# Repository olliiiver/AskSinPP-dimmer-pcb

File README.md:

# Homematic 5-channel LED dimmer PCB for Arduino using CC1101 (KiCad)

Arduino sketch can be found here:

https://github.com/olliiiver/AskSinPP-rgbwwcw-dimmer

## Features

- 12-24 volt
- 256-step 97 kHz PWM
- TTH or SMD for filter capacitors 

## BOM

- PCA9634PW
- Arduino Pro Mini https://store.arduino.cc/arduino-pro-mini
- CC1101 board (from eBay)
- N-Channel MOSFET (IRL540N 30A 100V)
- Recom R-78E5.0-0.5
- AMS1117-3.3
- 10K resistors
- 100 nF / 10 uF capacitors

## TODO

- Add ground pad

## Images

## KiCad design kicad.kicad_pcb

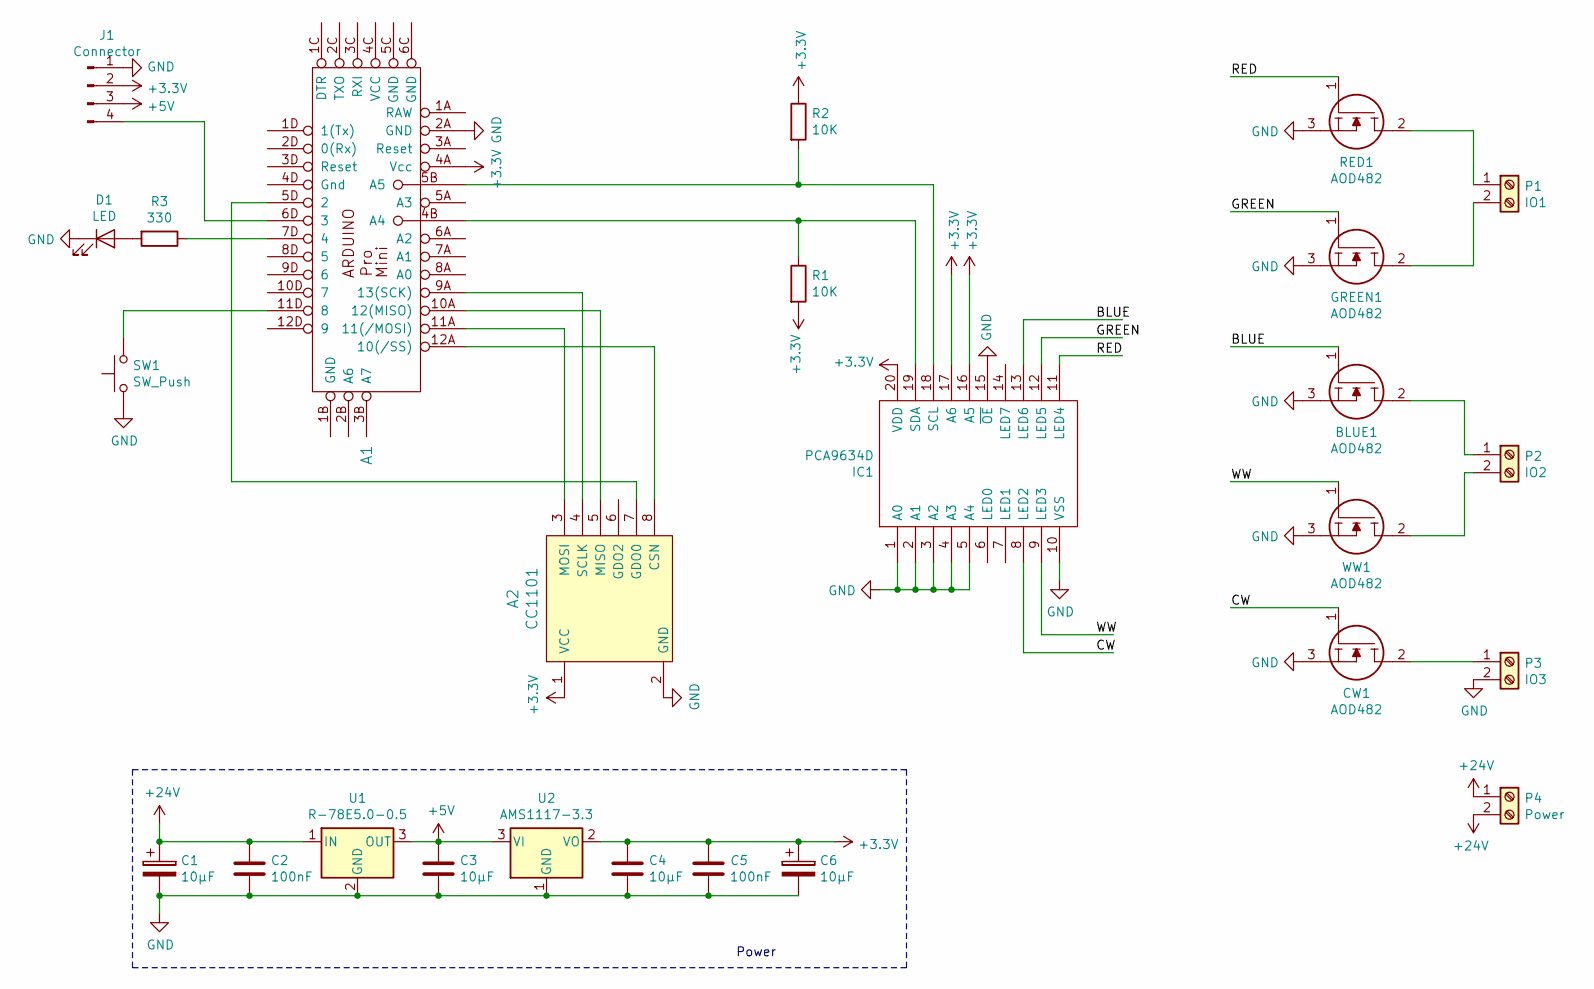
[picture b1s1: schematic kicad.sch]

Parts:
A1: Arduino_Pro_Mini
A2: CC1101; cc1101
BLUE1: AOD482; TO-252-2; Manufacturer_Part_Number IRL540NPBF; Mouser Part Number 942-IRL540NPBF
C1, C6: 10µF; CP_Radial_D5.0mm_P2.00mm
C2, C5: 100nF; C_Disc_D3.0mm_W2.0mm_P2.50mm
C3, C4: 10µF; C_0805_2012Metric_Pad1.15x1.40mm_HandSolder
CW1: AOD482; TO-252-2; Manufacturer_Part_Number IRL540NPBF; Mouser Part Number 942-IRL540NPBF
D1: LED; LED_D3.0mm
GREEN1: AOD482; TO-252-2; Manufacturer_Part_Number IRL540NPBF; Mouser Part Number 942-IRL540NPBF
IC1: PCA9634D; Manufacturer_Part_Number PCA9634D; Mouser Part Number 771-PCA9634D
J1: Connector; PinHeader_1x04_P2.54mm_Vertical
P1: IO1; TerminalBlock_bornier-2_P5.08mm
P2: IO2; TerminalBlock_bornier-2_P5.08mm
P3: IO3; TerminalBlock_bornier-2_P5.08mm
P4: Power; TerminalBlock_bornier-2_P5.08mm
R1, R2: 10K; R_0805_2012Metric_Pad1.15x1.40mm_HandSolder
R3: 330; R_0805_2012Metric_Pad1.15x1.40mm_HandSolder
RED1: AOD482; TO-252-2; Manufacturer_Part_Number IRL540NPBF; Mouser Part Number 942-IRL540NPBF
SW1: SW_Push; SW_PUSH_6mm
U1: R-78E5.0-0.5; Converter_DCDC_RECOM_R-78E-0.5_THT
U2: AMS1117-3.3; SOT-223-3_TabPin2
WW1: AOD482; TO-252-2; Manufacturer_Part_Number IRL540NPBF; Mouser Part Number 942-IRL540NPBF

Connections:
+3V3: A1.4A (Vcc), A2.1 (VCC), C4.1, C5.1, C6.1, IC1.16 (A5), IC1.17 (A6), IC1.20 (VDD), J1.2, R1.2, R2.1, U2.2 (VO)
+5V: C3.1, J1.3, U1.3 (OUT), U2.3 (VI)
+24V: C1.1, C2.1, P4.1, P4.2, U1.1 (IN)
/BLUE: BLUE1.1, IC1.13 (LED6)
/CW: CW1.1, IC1.8 (LED2)
/GREEN: GREEN1.1, IC1.12 (LED5)
/RED: IC1.11 (LED4), RED1.1
/WW: IC1.9 (LED3), WW1.1
GND: A1.2A (GND), A2.2 (GND), BLUE1.3, C1.2, C2.2, C3.2, C4.2, C5.2, C6.2, CW1.3, D1.1 (K), GREEN1.3, IC1.1 (A0), IC1.2 (A1), IC1.3 (A2), IC1.4 (A3), IC1.5 (A4), IC1.10 (VSS), IC1.15 (~OE), J1.1, P3.2, RED1.3, SW1.1, U1.2 (GND), U2.1 (GND), WW1.3
unnamed: A1.4B (A4), IC1.19 (SDA), R1.1
unnamed: A1.5B (A5), IC1.18 (SCL), R2.2
unnamed: A1.5D (2), A2.7 (GDO0)
unnamed: A1.6D (3), J1.4
unnamed: A1.7D (4), R3.1
unnamed: A1.9A (13(SCK)), A2.4 (SCLK)
unnamed: A1.10A (12(MISO)), A2.5 (MISO)
unnamed: A1.11A (11(/MOSI)), A2.3 (MOSI)
unnamed: A1.11D (8), SW1.2
unnamed: A1.12A (10(/SS)), A2.8 (CSN)
unnamed: BLUE1.2, P2.1
unnamed: CW1.2, P3.1
unnamed: D1.2 (A), R3.2
unnamed: GREEN1.2, P1.2
unnamed: P1.1, RED1.2
unnamed: P2.2, WW1.2

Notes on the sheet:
Power

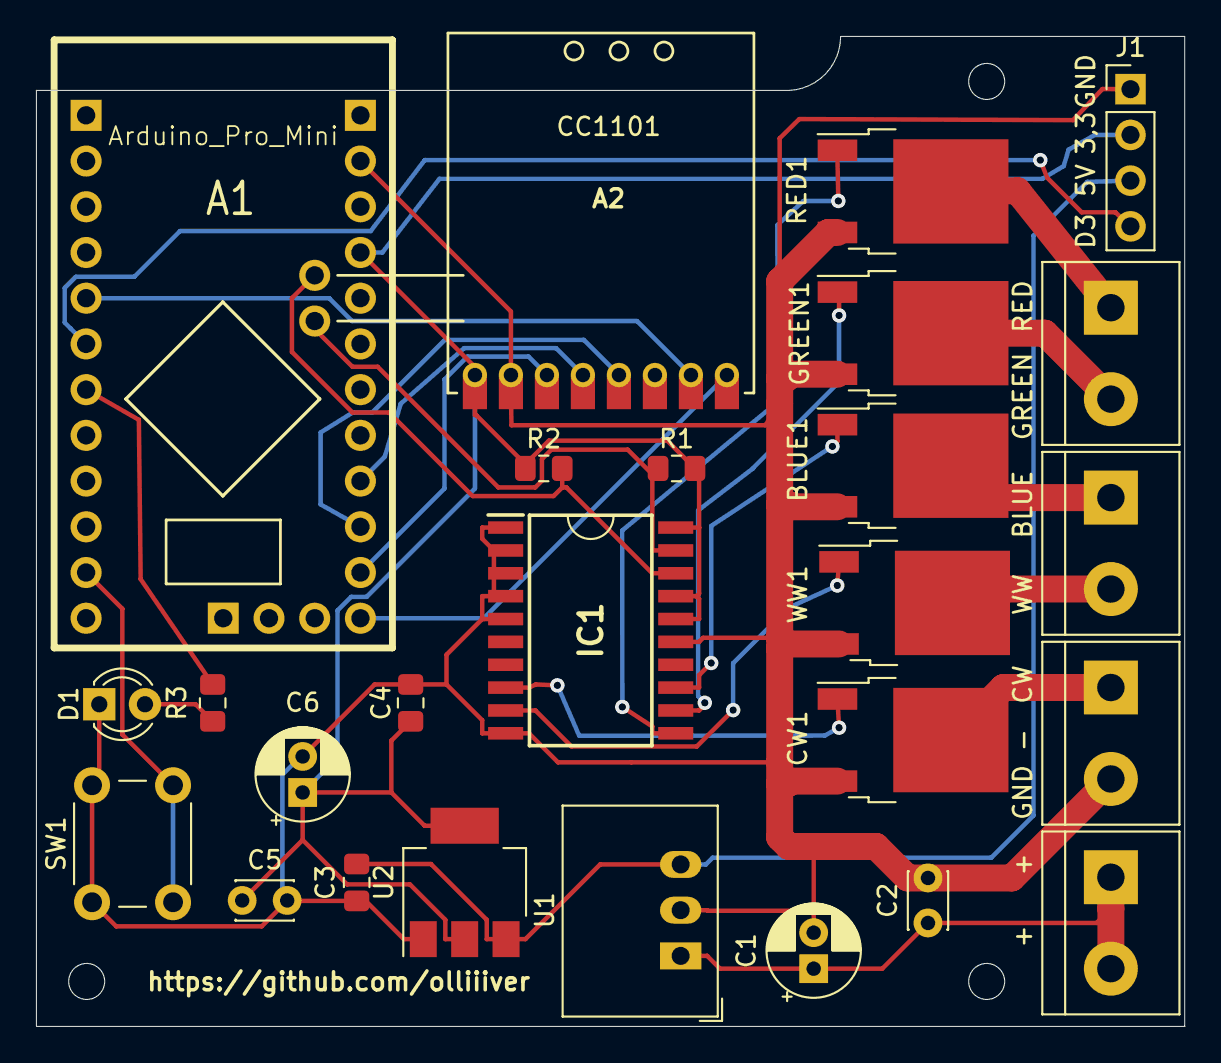
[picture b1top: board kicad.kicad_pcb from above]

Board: 2 copper layers, 63.8 x 55.0 mm, 29 parts (0 on the bottom side), 25 nets.

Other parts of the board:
MO1, MO2, MO3: MountingHole_2mm

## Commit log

2020-02-16 readme
